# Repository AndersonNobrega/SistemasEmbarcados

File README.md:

# Controlador de Brassagem para Cerveja

>Brassagem é o processo de combinação de uma mistura de grãos, conhecido como o "grãos de lei", e água, denominada como "licor", sendo esta mistura aquecida. Sobretudo, o projeto em questão tem como intuito a construção de um PCB para controle de deste processo, além disso foram desenvolvidos firmwares e diagramas para uma melhor compreensão da abstração do problema.

### Etapas de desenvolvimento

O projeto de disciplina passsou por etapas a serem desenvolvidas, foram essas etapas as seguintes:

- [x] Construir esquemático e board no Eagle
- [x] Construir diagrama para explanação
- [x] Construir o firmware para aplicação
- [x] Produzir um vídeo para demonstrar o objetivo do projeto
- [x] Construir um documento sobre o projeto 

## 💻 Pré-requisitos

Antes de começar, verifique se você atendeu aos seguintes requisitos:
* Você instalou uma versão do `Eagle`
* Você tem uma máquina `Windows`. 
* Você leu `guia ou vídeo de explanação`.
* Você instalou a plataforma do `Arduino`

## 🚀 Instalando o Controlador de Brassagem para Cerveja

Para instalar o Controlador de Brassagem para Cerveja, siga estas etapas:

Windows:
```
Acesse a Plataforma do Arduino e importe o arquivo controladorBrassagem.ino, localizado no arquivo Firmware.
```

## ☕ Usando Controlador de Cerveja

Para usar Controlador de Cerveja, siga estas etapas:

- Após importar o firmware em sua IDE, garanta que sua IDE está funcionando corretamente e verificando as importações, e logo em seguida, aperte o play.
-  Após verificar que o firwmare foi compilado com sucesso, simule-o com suas configurações desejadas.
-  Importe-o ao seu circuito e sumule seu cenário.
---
## Link explanação - Youtube
Link do Youtube - https://youtu.be/oVvX4KhvvNE
## 🤝 Colaboradores
---
Agradecemos às seguintes pessoas que contribuíram para este projeto:
---
<table>
  <tr>
    <td align="center">
      <a href="#">
        <br>
        <sub>
          <b>Anderson Nóbrega</b>
        </sub>
      </a>
    </td>
    <td align="center">
      <a href="#">
        <br>
        <sub>
          <b>João Soares</b>
        </sub>
      </a>
    </td>
  </tr>
</table>

[⬆ Voltar ao topo](#nome-do-projeto)<br>

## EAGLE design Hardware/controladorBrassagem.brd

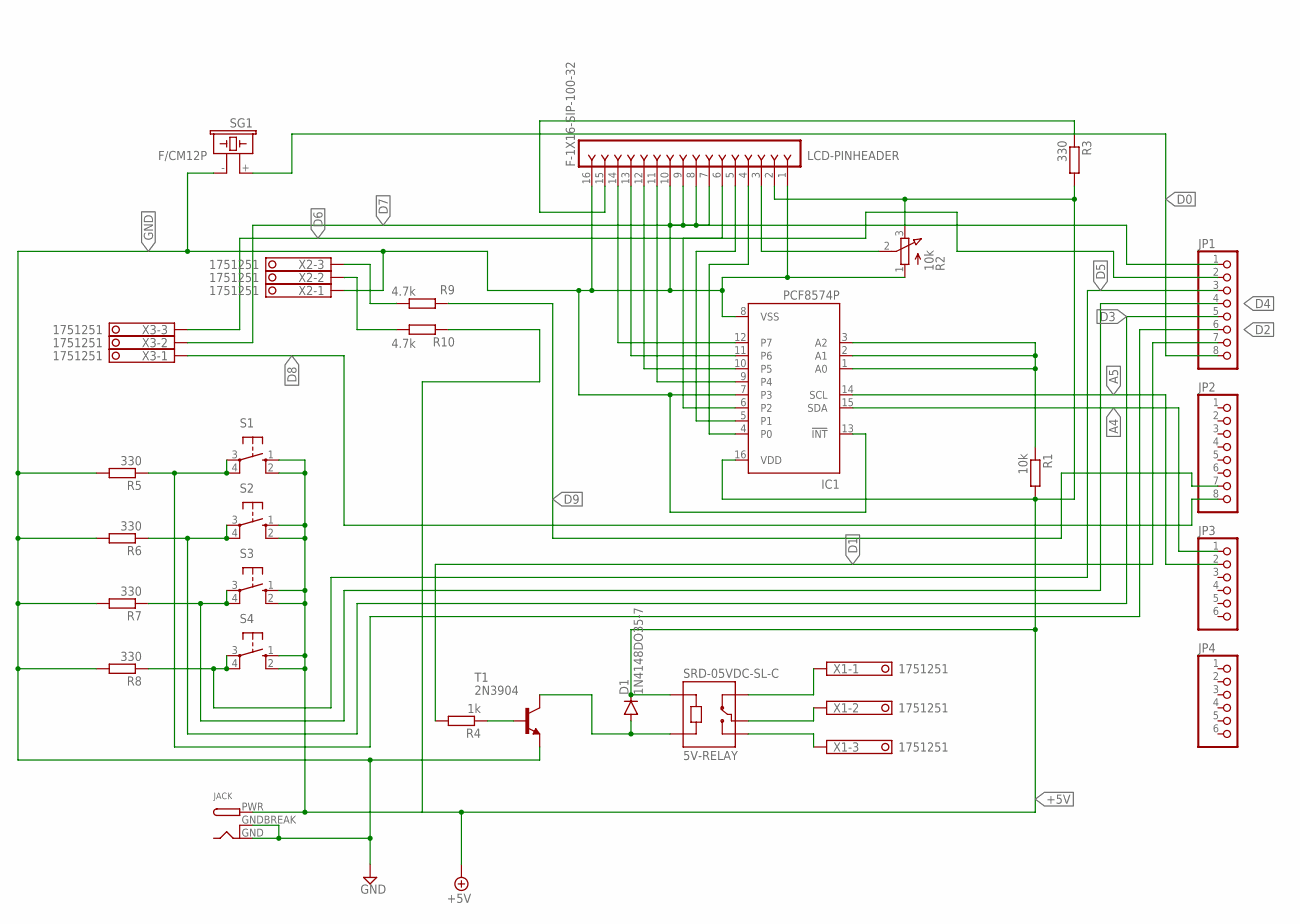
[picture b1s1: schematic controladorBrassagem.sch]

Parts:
5V-RELAY: SRD-05VDC-SL-C; RELAY_SRD-05VDC-SL-C
D1: 1N4148DO35-7; DO35-7
IC1: PCF8574P; DIL16
JACK: DCBARRELPTH; DCJACK_2MM_PTH
JP1, JP2: PINHD-1X8; 1X08
JP3, JP4: PINHD-1X6; 1X06
LCD-PINHEADER: F-1X16-SIP-100-32; SIP-100-16-32
R1: 10k; 0207/10
R2: 10k; 3RP/1610N
R3, R5, R6, R7, R8: 330; 0207/10
R4: 1k; 0207/10
R9, R10: 4.7k; 0207/10
S1, S2, S3, S4: 10-XX; B3F-10XX
SG1: F/CM12P
T1: 2N3904; TO92
X1, X2, X3: 1751251

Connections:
+5V: 5V-RELAY.A2, D1.C, IC1.16 (VDD), JACK.PWR, LCD-PINHEADER.2, R1.2, R2.3 (E), R3.2, R10.1, S1.1 (S), S1.2 (S1), S2.1 (S), S2.2 (S1), S3.1 (S), S3.2 (S1), S4.1 (S), S4.2 (S1)
A4: IC1.15 (SDA), JP3.1
A5: IC1.14 (SCL), JP3.2
D0: JP1.8, SG1.+ (1)
D1: JP1.7, R4.2
D2: JP1.6, R5.1, S1.3, S1.4 (P1)
D3: JP1.5, R6.1, S2.3, S2.4 (P1)
D4: JP1.4, R7.1, S3.3, S3.4 (P1)
D5: JP1.3, R8.1, S4.3, S4.4 (P1)
D6: JP1.2, X3.3
D7: JP1.1, X3.2
D8: JP2.8, X3.1
D9: JP2.7, R9.1
GND: IC1.7 (P3), IC1.8 (VSS), IC1.13 (!INT), JACK.GND, JACK.GNDBREAK, LCD-PINHEADER.1, LCD-PINHEADER.7, LCD-PINHEADER.8, LCD-PINHEADER.9, LCD-PINHEADER.10, LCD-PINHEADER.16, R2.1 (A), R5.2, R6.2, R7.2, R8.2, SG1.- (2), T1.3 (E), X2.1
unnamed: IC1.1 (A0), IC1.2 (A1), IC1.3 (A2), R1.1
unnamed: LCD-PINHEADER.3, R2.2 (S)
unnamed: IC1.4 (P0), LCD-PINHEADER.4
unnamed: IC1.5 (P1), LCD-PINHEADER.5
unnamed: IC1.6 (P2), LCD-PINHEADER.6
unnamed: IC1.9 (P4), LCD-PINHEADER.11
unnamed: IC1.10 (P5), LCD-PINHEADER.12
unnamed: IC1.11 (P6), LCD-PINHEADER.13
unnamed: IC1.12 (P7), LCD-PINHEADER.14
unnamed: LCD-PINHEADER.15, R3.1
unnamed: R9.2, X2.3
unnamed: R4.1, T1.2 (B)
unnamed: 5V-RELAY.A1, D1.A, T1.1 (C)
unnamed: 5V-RELAY.NC, X1.1
unnamed: 5V-RELAY.COM, X1.2
unnamed: 5V-RELAY.NO, X1.3
unnamed: R10.2, X2.2

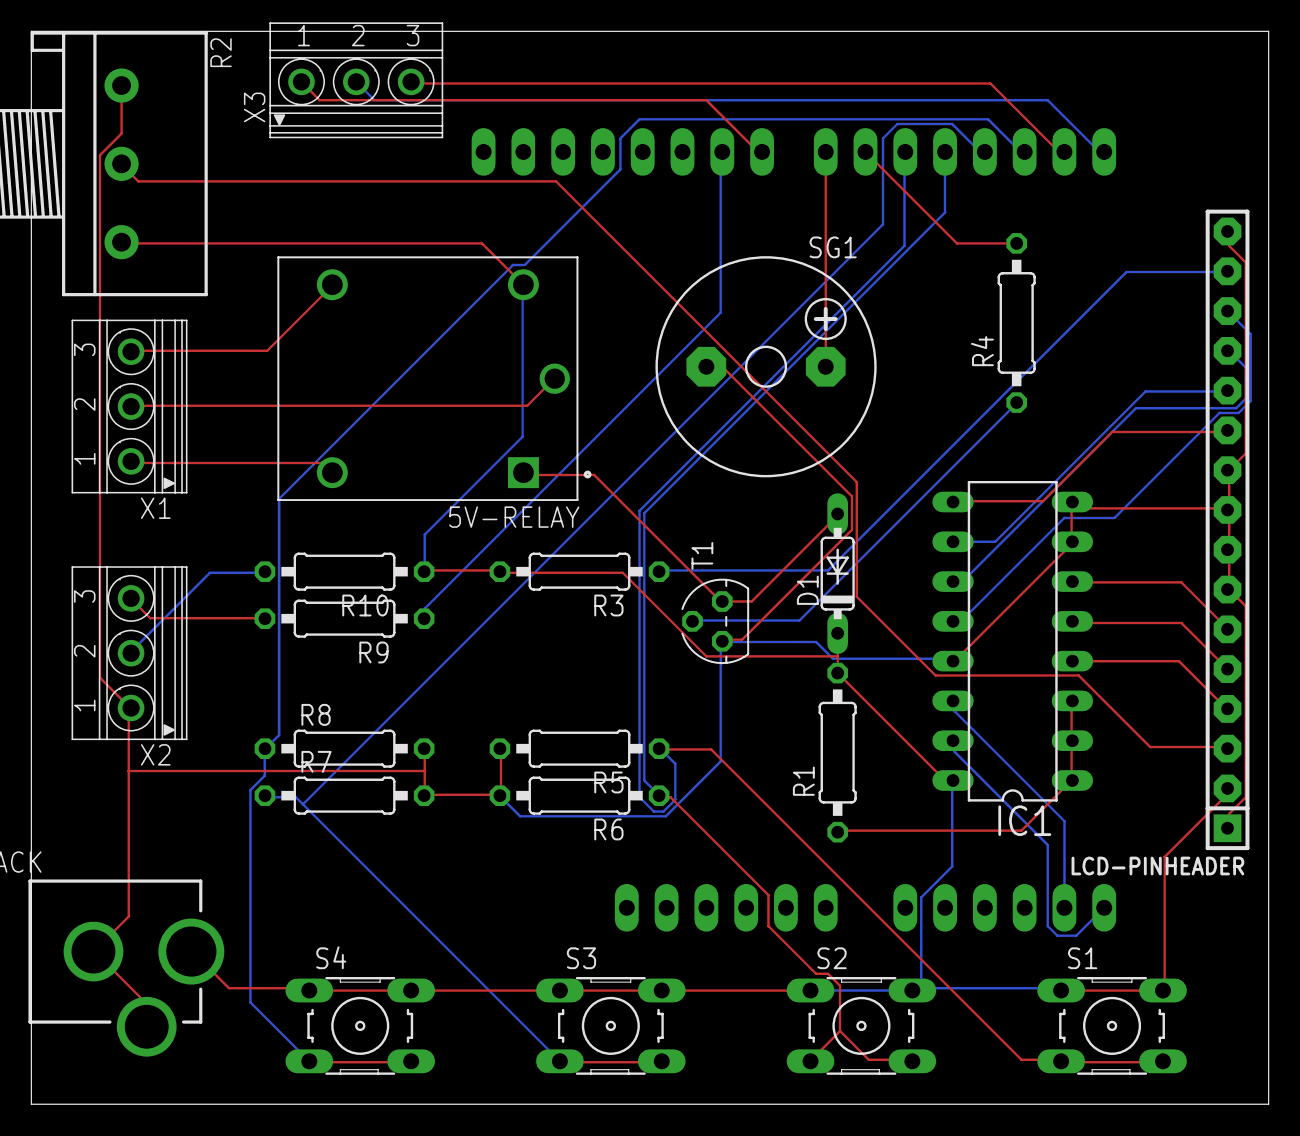
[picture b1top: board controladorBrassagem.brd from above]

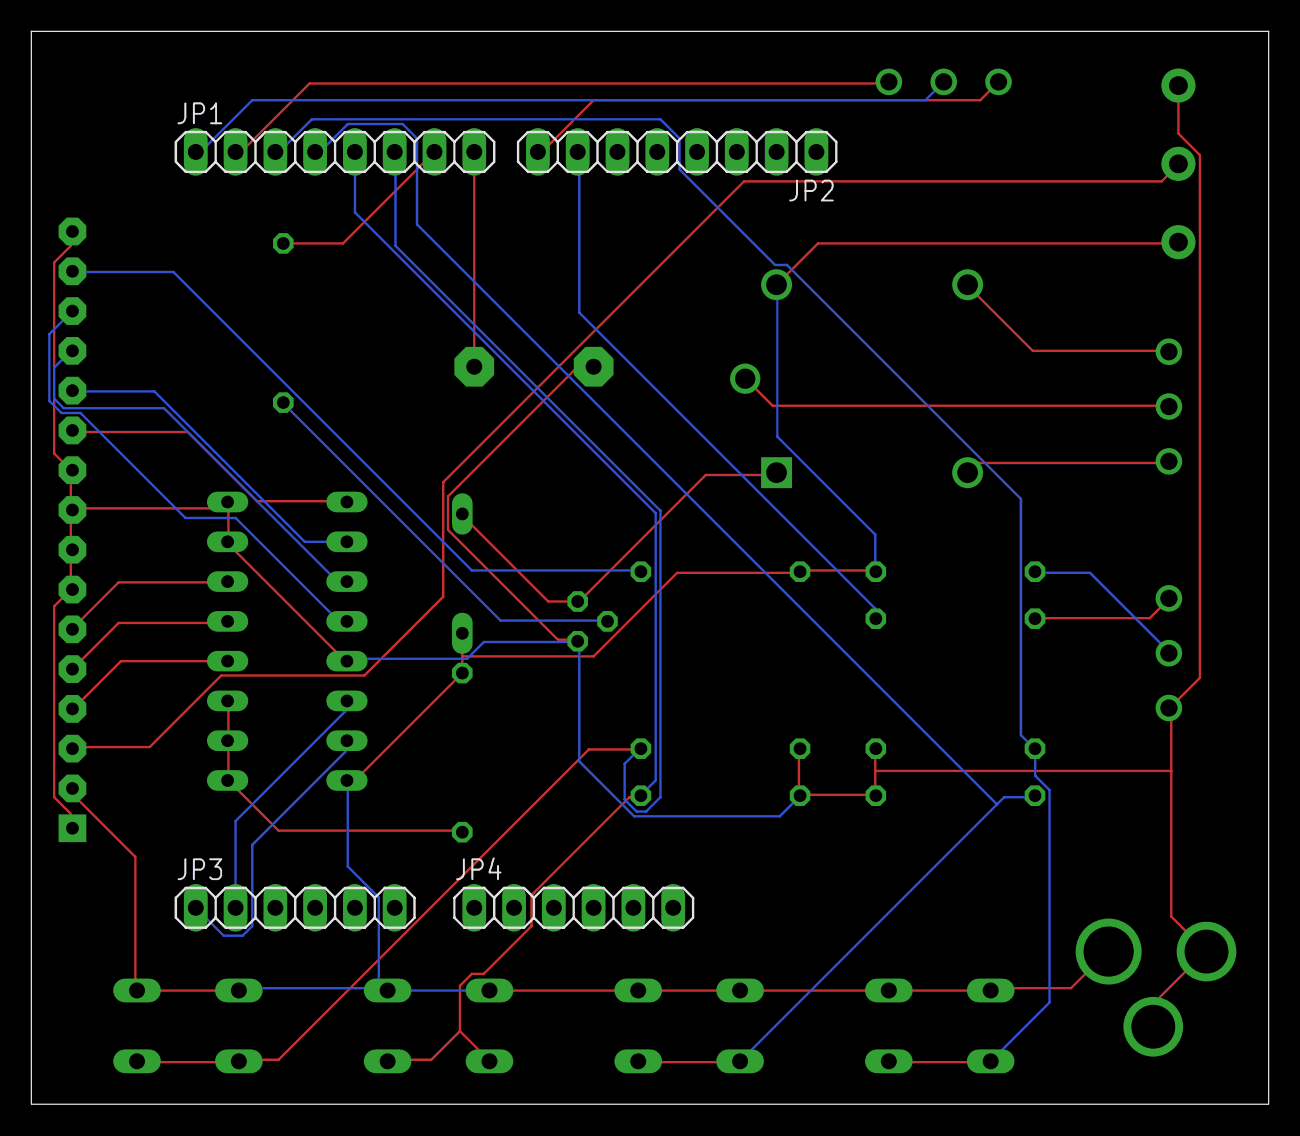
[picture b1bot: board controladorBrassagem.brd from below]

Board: 2 copper layers, 79.0 x 68.5 mm, 28 parts (4 on the bottom side), 31 nets.

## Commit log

2021-05-23 Adicionando arquivos do projeto
2021-05-23 Alterando firmware

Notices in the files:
parts and their libraries:
con-headers-jp: Copyright (C) 2008, Bob Starr
